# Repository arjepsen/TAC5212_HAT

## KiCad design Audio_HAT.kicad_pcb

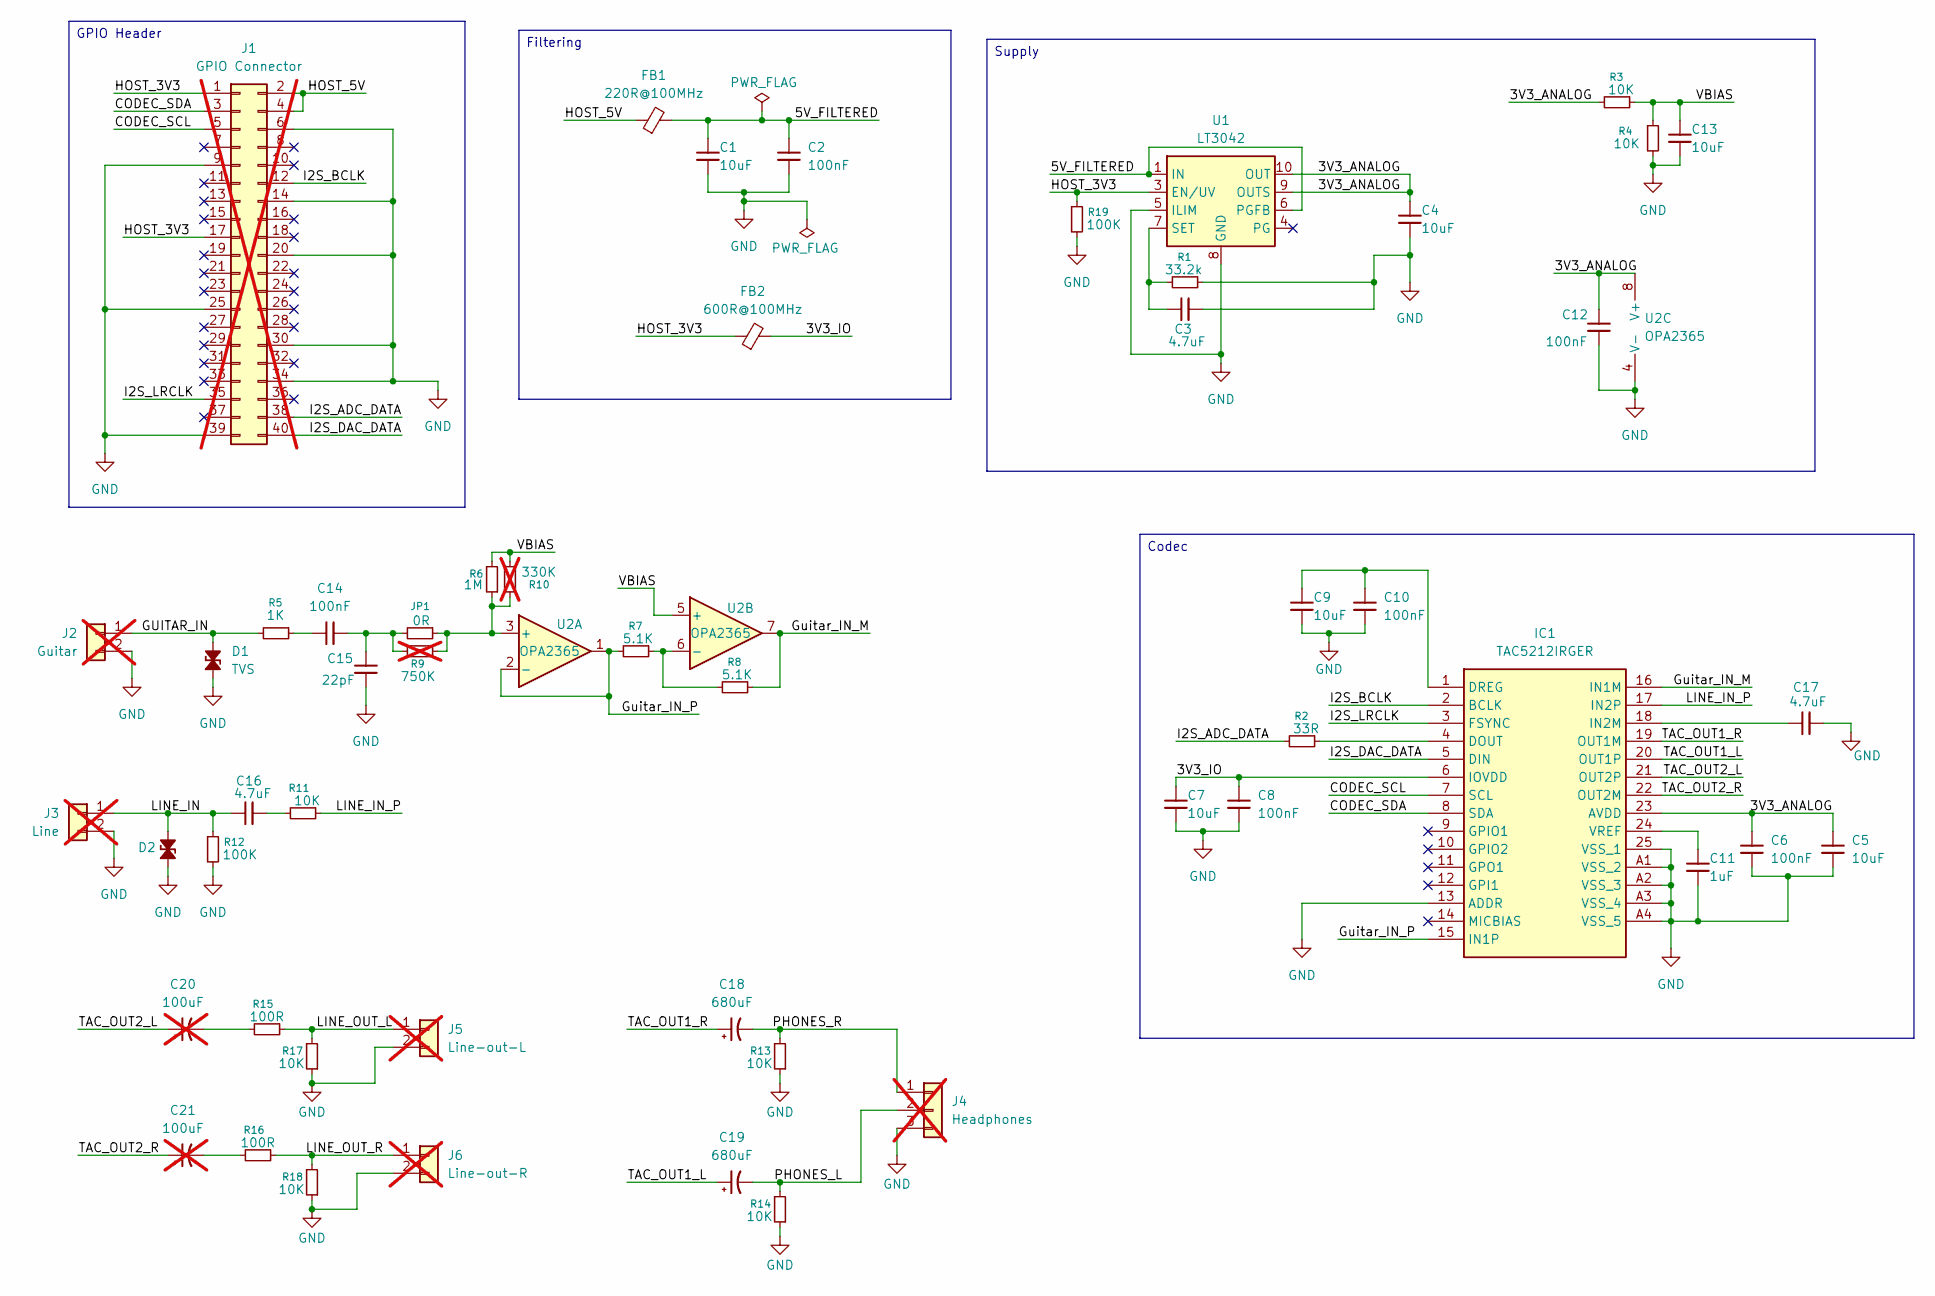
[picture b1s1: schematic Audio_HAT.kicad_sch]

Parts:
C1, C4, C5, C7, C9, C13: 10uF; C_0805_2012Metric; Manufacturer part CL21A106KAYNNNE; JLCPCB part C15850
C2, C6, C8, C10, C12: 100nF; C_0603_1608Metric; Manufacturer part CC0603KRX7R9BB104; JLCPCB part C14663
C3: 4.7uF; C_0805_2012Metric; Manufacturer part CL21A475KAQNNNE; JLCPCB part C1779
C11: 1uF; C_0805_2012Metric; Manufacturer part CL21B105KBFNNNE; JLCPCB part C28323
C14: 100nF; C_1206_3216Metric; Manufacturer part 1206CG104J500NT; JLCPCB part C46348
C15: 22pF; C_0603_1608Metric; Manufacturer part CL10C220JB8NNNC; JLCPCB part C1653
C16, C17: 4.7uF; C_1206_3216Metric; Manufacturer part 1206B475K500NT; JLCPCB part C29823
C18, C19: 680uF; CP_Radial_D8.0mm_P3.50mm; Manufacturer part EEU-FR1A681; JLCPCB part C407875
C20, C21: 100uF; CP_Radial_D5.0mm_P2.00mm; Manufacturer part EEU-FR1C101; JLCPCB part C278532; not fitted
D1, D2: TVS; D_SOD-523; Manufacturer part PESD5V0U1BB,115; JLCPCB part C85388
FB1: 220R@100MHz; L_0805_2012Metric; Manufacturer Part BLM21PG221SN1D
FB2: 600R@100MHz; L_0603_1608Metric; Manufacturer Part BLM18SP601SN1D
IC1: TAC5212IRGER; TAC5212IRGER_Custom; Manufacturer part TAC5212IRGER; JLCPCB part C44853694
J1: GPIO Connector; PinSocket_2x20_P2.54mm_Vertical; Manufacturer part 2.54-2*20; JLCPCB part C2977589; not fitted
J2: Guitar; Wire_0.15mm2_1x02_P2.54mm_D0.8mm; not fitted
J3: Line; Wire_0.15mm2_1x02_P2.54mm_D0.8mm; not fitted
J4: Headphones; Wire_0.15mm2_1x03_P2.54mm_D0.8mm; not fitted
J5: Line-out-L; Wire_0.15mm2_1x02_P2.54mm_D0.8mm; not fitted
J6: Line-out-R; Wire_0.15mm2_1x02_P2.54mm_D0.8mm; not fitted
JP1: 0R; R_0603_1608Metric; Manufacturer part RC0603JR-070RL; JLCPCB part C21189
R1: 33.2k; R_0603_1608Metric; Manufacturer part RT0603BRD0733K2L; JLCPCB part C705767
R2: 33R; R_0402_1005Metric; Manufacturer part RC0402FR-0733RL; JLCPCB part C25105
R3, R4: 10K; R_0603_1608Metric; Manufacturer part RC0603FR-0710KL; JLCPCB part C25804
R5: 1K; R_0603_1608Metric; Manufacturer part RC0603FR-071KL; JLCPCB part C21190
R6: 1M; R_0603_1608Metric; Manufacturer part 0603WAF1004T5E; JLCPCB part C22935
R7, R8: 5.1K; R_0603_1608Metric; Manufacturer part CRCW06035K10FKEA; JLCPCB part C23186
R9: 750K; R_0603_1608Metric; Manufacturer part RC0603FR-07750KL; JLCPCB part C137684; not fitted
R10: 330K; R_0603_1608Metric; Manufacturer part 0603WAF3303T5E; JLCPCB part C23137; not fitted
R11, R13, R14, R17, R18: 10K; R_0402_1005Metric; Manufacturer part RC0402FR-0710KL; JLCPCB part C25744
R12: 100K; R_0603_1608Metric; Manufacturer part RC0603FR-07100KL; JLCPCB part C25803
R15, R16: 100R; R_0402_1005Metric; Manufacturer part RC0402FR-07100RL; JLCPCB part C25076
R19: 100K; R_0402_1005Metric; Manufacturer part RC0402FR-07100KL; JLCPCB part C25741
U1: LT3042; MSOP-10-1EP_3x3mm_P0.5mm_EP1.68x1.88mm; MPN LT3042EMSE#PBF
U2: OPA2365; SOIC-8_3.9x4.9mm_P1.27mm; Manufacturer part OPA2365AIDR; JLCPCB part C130011

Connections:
/3V3_ANALOG: C4.1, C5.1, C6.1, C12.1, IC1.23 (AVDD), R3.2, U1.9 (OUTS), U1.10 (OUT), U2.8 (V+)
/3V3_IO: C7.1, C8.1, FB2.2, IC1.6 (IOVDD)
/5V_FILTERED: C1.1, C2.1, FB1.2, U1.1 (IN), U1.2 (IN), U1.6 (PGFB)
/CODEC_SCL: IC1.7 (SCL), J1.5
/CODEC_SDA: IC1.8 (SDA), J1.3
/GUITAR_IN: D1.2 (A2), J2.1, R5.2
/Guitar_IN_M: IC1.16 (IN1M), R8.1, U2.7
/Guitar_IN_P: IC1.15 (IN1P), R7.2, U2.1, U2.2 (-)
/HOST_3V3: FB2.1, J1.1, J1.17, R19.1, U1.3 (EN/UV)
/HOST_5V: FB1.1, J1.2, J1.4
/I2S_ADC_DATA: J1.38, R2.2
/I2S_BCLK: IC1.2 (BCLK), J1.12
/I2S_DAC_DATA: IC1.5 (DIN), J1.40
/I2S_LRCLK: IC1.3 (FSYNC), J1.35
/LINE_IN: C16.1, D2.2 (A2), J3.1, R12.1
/LINE_IN_P: IC1.17 (IN2P), R11.1
/LINE_OUT_L: J5.1, R15.1, R17.2
/LINE_OUT_R: J6.1, R16.1, R18.2
/PHONES_L: C19.2, J4.2, R14.2
/PHONES_R: C18.2, J4.1, R13.2
/TAC_OUT1_L: C19.1, IC1.20 (OUT1P)
/TAC_OUT1_R: C18.1, IC1.19 (OUT1M)
/TAC_OUT2_L: C20.1, IC1.21 (OUT2P)
/TAC_OUT2_R: C21.1, IC1.22 (OUT2M)
/VBIAS: C13.1, R3.1, R4.1, R6.2, R10.2, U2.5 (+)
GND: C1.2, C2.2, C3.2, C4.2, C5.2, C6.2, C7.2, C8.2, C9.2, C10.2, C11.2, C12.2, C13.2, C15.2, C17.2, D1.1 (A1), D2.1 (A1), IC1.13 (ADDR), IC1.25 (VSS_1), IC1.A1 (VSS_2), IC1.A2 (VSS_3), IC1.A3 (VSS_4), IC1.A4 (VSS_5), J1.6, J1.9, J1.14, J1.20, J1.25, J1.30, J1.34, J1.39, J2.2, J3.2, J4.3, J5.2, J6.2, R1.1, R4.2, R12.2, R13.1, R14.1, R17.1, R18.1, R19.2, U1.5 (ILIM), U1.8 (GND), U1.11 (GND), U2.4 (V-)
unnamed: C14.1, R5.1
unnamed: C14.2, C15.1, JP1.2, R9.2
unnamed: C16.2, R11.2
unnamed: C20.2, R15.2
unnamed: C21.2, R16.2
unnamed: IC1.4 (DOUT), R2.1
unnamed: C9.1, C10.1, IC1.1 (DREG)
unnamed: C17.1, IC1.18 (IN2M)
unnamed: C11.1, IC1.24 (VREF)
unnamed: C3.1, R1.2, U1.7 (SET)
unnamed: JP1.1, R6.1, R9.1, R10.1, U2.3 (+)
unnamed: R7.1, R8.2, U2.6 (-)

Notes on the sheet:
Codec
Supply
GPIO Header
Filtering

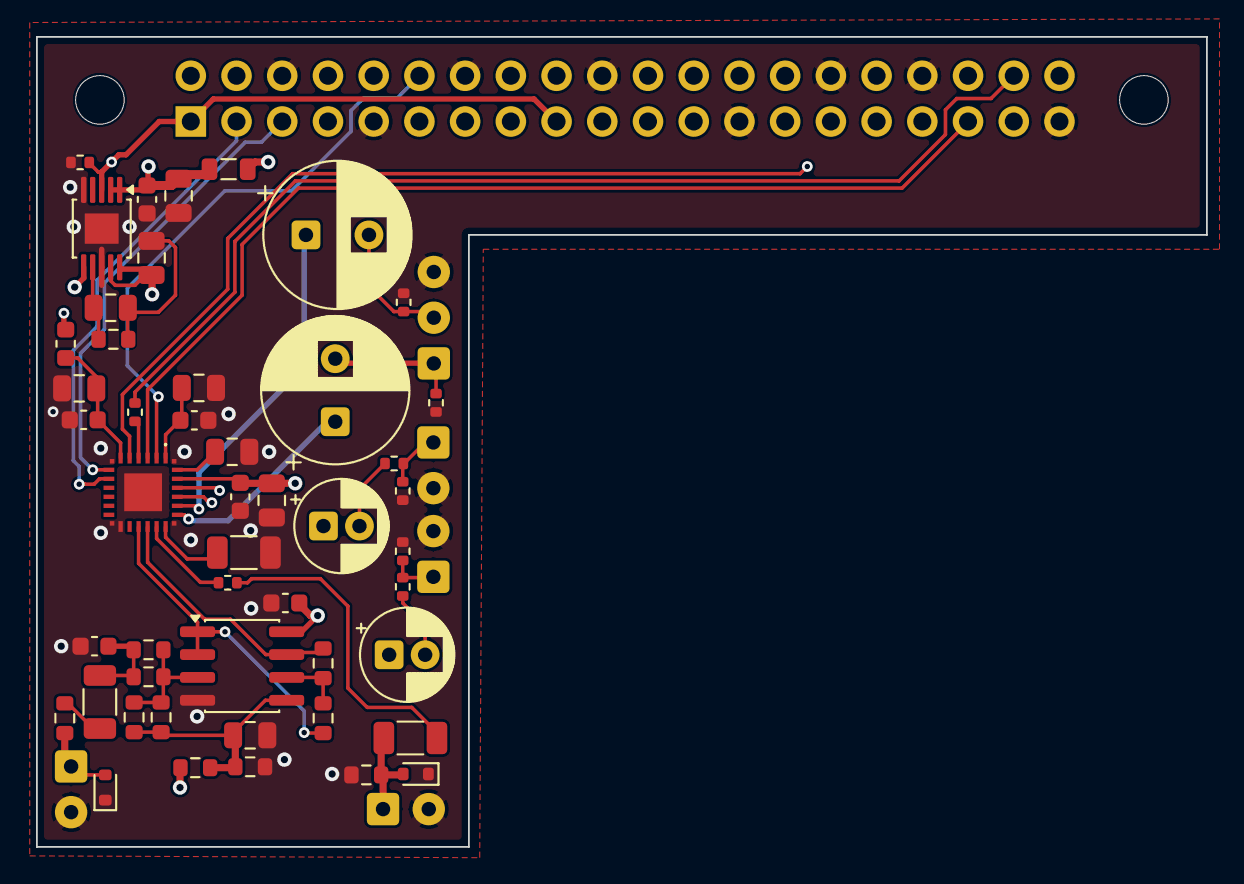
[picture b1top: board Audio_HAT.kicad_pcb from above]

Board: 4 copper layers, 65.0 x 45.0 mm, 54 parts (1 on the bottom side), 38 nets.

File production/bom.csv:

Designator,Footprint,Quantity,Value,LCSC Part #
"C1, C13, C4, C5, C7, C9",0805,6,10uF,CL21A106KAYNNNE
"C10, C12, C2, C6, C8",0603,5,100nF,CC0603KRX7R9BB104
C11,0805,1,1uF,CL21B105KBFNNNE
C14,1206,1,100nF,1206CG104J500NT
C15,0603,1,22pF,CL10C220JB8NNNC
"C16, C17",1206,2,4.7uF,1206B475K500NT
"C18, C19",CP_Radial_D8.0mm_P3.50mm,2,680uF,EEU-FR1A681
C3,0805,1,4.7uF,CL21A475KAQNNNE
"D1, D2",D_SOD-523,2,TVS,"PESD5V0U1BB,115"
FB1,0805,1,220R@100MHz,BLM21PG221SN1D
FB2,0603,1,600R@100MHz,BLM18SP601SN1D
IC1,TAC5212IRGER_Custom,1,TAC5212IRGER,TAC5212IRGER
JP1,0603,1,0R,RC0603JR-070RL
R1,0603,1,33.2k,RT0603BRD0733K2L
"R11, R13, R14, R17, R18",0402,5,10K,RC0402FR-0710KL
R12,0603,1,100K,RC0603FR-07100KL
"R15, R16",0402,2,100R,RC0402FR-07100RL
R19,0402,1,100K,RC0402FR-07100KL
R2,0402,1,33R,RC0402FR-0733RL
"R3, R4",0603,2,10K,RC0603FR-0710KL
R5,0603,1,1K,RC0603FR-071KL
R6,0603,1,1M,0603WAF1004T5E
"R7, R8",0603,2,5.1K,CRCW06035K10FKEA
U1,MSOP-10-1EP_3x3mm_P0.5mm_EP1.68x1.88mm,1,LT3042,LT3042EMSE#PBF
U2,SOIC-8_3.9x4.9mm_P1.27mm,1,OPA2365,OPA2365AIDR
